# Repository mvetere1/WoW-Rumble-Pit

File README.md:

## Rumble Pit WoW Addon and hardware
### Objective: Make a device that can read data out of the world of warcraft game and adjust a motorized rumble pack based on damage done to give player live feedback 

#### Limitations
The game does not allow data to be streamed out while combat is happening.  Only after combat can logs etc be read to figure out damage done by the group.  Alledgely this is to deter botters from extracting too much data out of game live.  Addons are able to efficiently proceess data in-game to give good stats for group damage.

### 1. Initial Thoughts and Development
#### Motor Control
The motorized rumble pack control is pretty straightforward and not likely to change. A DC motor controller lets you control the speed of a motor by powering a high amperage motor with a low amperage signal from a micontroller.  The 293D is a really popular bidirectional motor control chip for <600ma at 4.5v-36v.   Using pulse-width modulation, you basically power the motor in short bursts.  The slower you want the motor, the longer the power is off.  If you want the max speed, the motor is powered 100% of the time.  So to control the motor speed, you just need a signal that you can vary the on/off state fairly quickly.  Sources for images can be found in Usefulinks.txt.

####  Potential Audio Output
Because you are limited to extracting data from the software in a non-live way, a method using hardware could be used instead.
* Data might be able to get exported from the game in the form of live running mp3.  A series of mp3 files could be made that encodes the desired level of vibration (based on damage) that is read by a microntroller directly controller the rumble pack.  I figure the mp3 file could be direct recordings of a UART sending out 0->10 in binary.
  * Pros: Should be a pretty reliable form of communication, it's easy to play mp3 files in-game through a certain audio port
  * Cons: Mp3s would need to get pre-recorded, one for each power level so it could add up to a lot of mp3
#### Potential Optical Output
* Data could be exported from the game optically. The game could print a box on the screen and flash the box black/white in a way that is encoding power level for the rumble pack motor.  The most efficient way would do this is without a microntroller, it could flash pulses of white/black with varying duty-cycles to control the motor at different speeds.  A type of light sensor would act as the optical-> voltage transducer and could be mounted to the monitor.  
  * Pros - No microcontroller needed, less steps for processing
  * Cons - Light sensor needs to be sensitive/tunable enough to detect on-screen changes.  Timing with LUA would need to be consistent
  
Alternatively, the flashing could try to emulate the entirety of UART and the bits could be read from a microcontroller with the UART peripheral.  
  * Pros - Sending 8 bit packets would open huge doors for sending arbitrary data out of the game, UART supported by 99% of micros
  * Cons - Light sensor needs to be sensitive/tunable for on-screen changes, timing would be critical to control.
  
A third way would be the have the box adjust the shade of black or white.  That shade of color would correlate to a rumble power level.  A color sensor could be mounted to the screen and send the data to a micro.
  * Pros - Should be able to get decent resolution with color shading.  Wouldn't require precise timing within LUA scripts
  * Cons - Color sensing might need a lite-calibration.  Output data format for color is probably more complicated than voltage.
  
### 2.Options tried
#### Optical LED transitor circuit
The first method I tried was the first listed optical choice.  I wanted to see if a simple light detector circuit would be sensitive enough to detect a white box vs a black box on a computer screen.  Since I had the parts, I went with the following:

Transitor used was a common NPN 2N222.  The most sensitive combination of parts I found was an orange LED and a 470k resistor.  The higher the R, the more gain.  When light of the same color hits the led, a small current is generated, so with the transistor applying a large gain, the voltage at the collector can vary up to Vp to respond to changes in light.  When the LED in this circuit has another LED of the same type blasting full strength right next to it, the voltage drops to 0v.  When in just ambient light, voltage is 5v.  So if the white box on the screen put out enough light, to drop voltage to 0, this the timing of the light pulses could be used to PWM the motor to the correct speed.

The issue is that the LCD monitor does not put out enough light at the right frequency to have any voltage response that could be used for PWM of the motor.  Potentially a light detector circuit that is more appropriate just an led and transistor would work better but that is unavailable right now.

#### Optical Color light to frequency converter
I tried a module based on the TSC3200 chip that is used as a color sensor.    

Based on the selection for pin S2 and S3, you can detect how much of that color is present where the sensor/chip is pointing. If I have it set to red, a full red color will produce 370hz while black would produce 250hz.  A decent oscilloscope will show you apprximate frequency of the output.  So if you have 10 divisions, each divisions would have a range of ~12hz.  You would probably need to sample for 100ms+ to get a good average of frequency but the 10 levels could probably be done.  

There's also the option of switching the full scale output frequency at 2%, 20% or 100%.  The faster the frequency, the quicker  you can get an average of 100 cycles for example but the sampling device would need to be able to keep up.  I chose 2% because that is still 250hz+ so 100 cycles could be sampled in 400ms, defintely fast enough for this application.  Updating the motor speed 2 times a second would be pretty smooth.

This method seems to be the most viable to far but it would probably need a type of calibration because once you change position of the sensor pointed on the screen, the min/max frequency changes.  Tt probably has to do with the positioning and reflection off the screen.  After installing on the screen with ambient lighting running, you would get the max and min frequency switching from red to black.  You would then need to program this back into the microcontroller thats calculating frequency so you can properly map max frequency to 100% duty cycle for max motor speed.  The min frequency would be 0% duty cycle, no motor speed.

I decided to go with the red color selection at 2% full scale frequency, and am planning for black to be ~250hz and red to be ~370hz.  Going with 10 divisions (10%, 20%, 30%.. etc motor strength) means each power level will have a 12hz bucket.  I am interpolating the data here but in reality it might not be so linear.  The equation is: % Duty cycle = (output frequenxy[hz] - 250[hz])(0.8[%]/[hz]).  This equation would change depending on the specific frequencies that red and black produce on that particular setup.

#### Microntroller Frequency Counting

The output of the sensor needs to be plugged into something that can convert the frequency into a PWN signal.  Based on the one off nature of this project, I'm going with an arduino uno.  
update 05Jun20

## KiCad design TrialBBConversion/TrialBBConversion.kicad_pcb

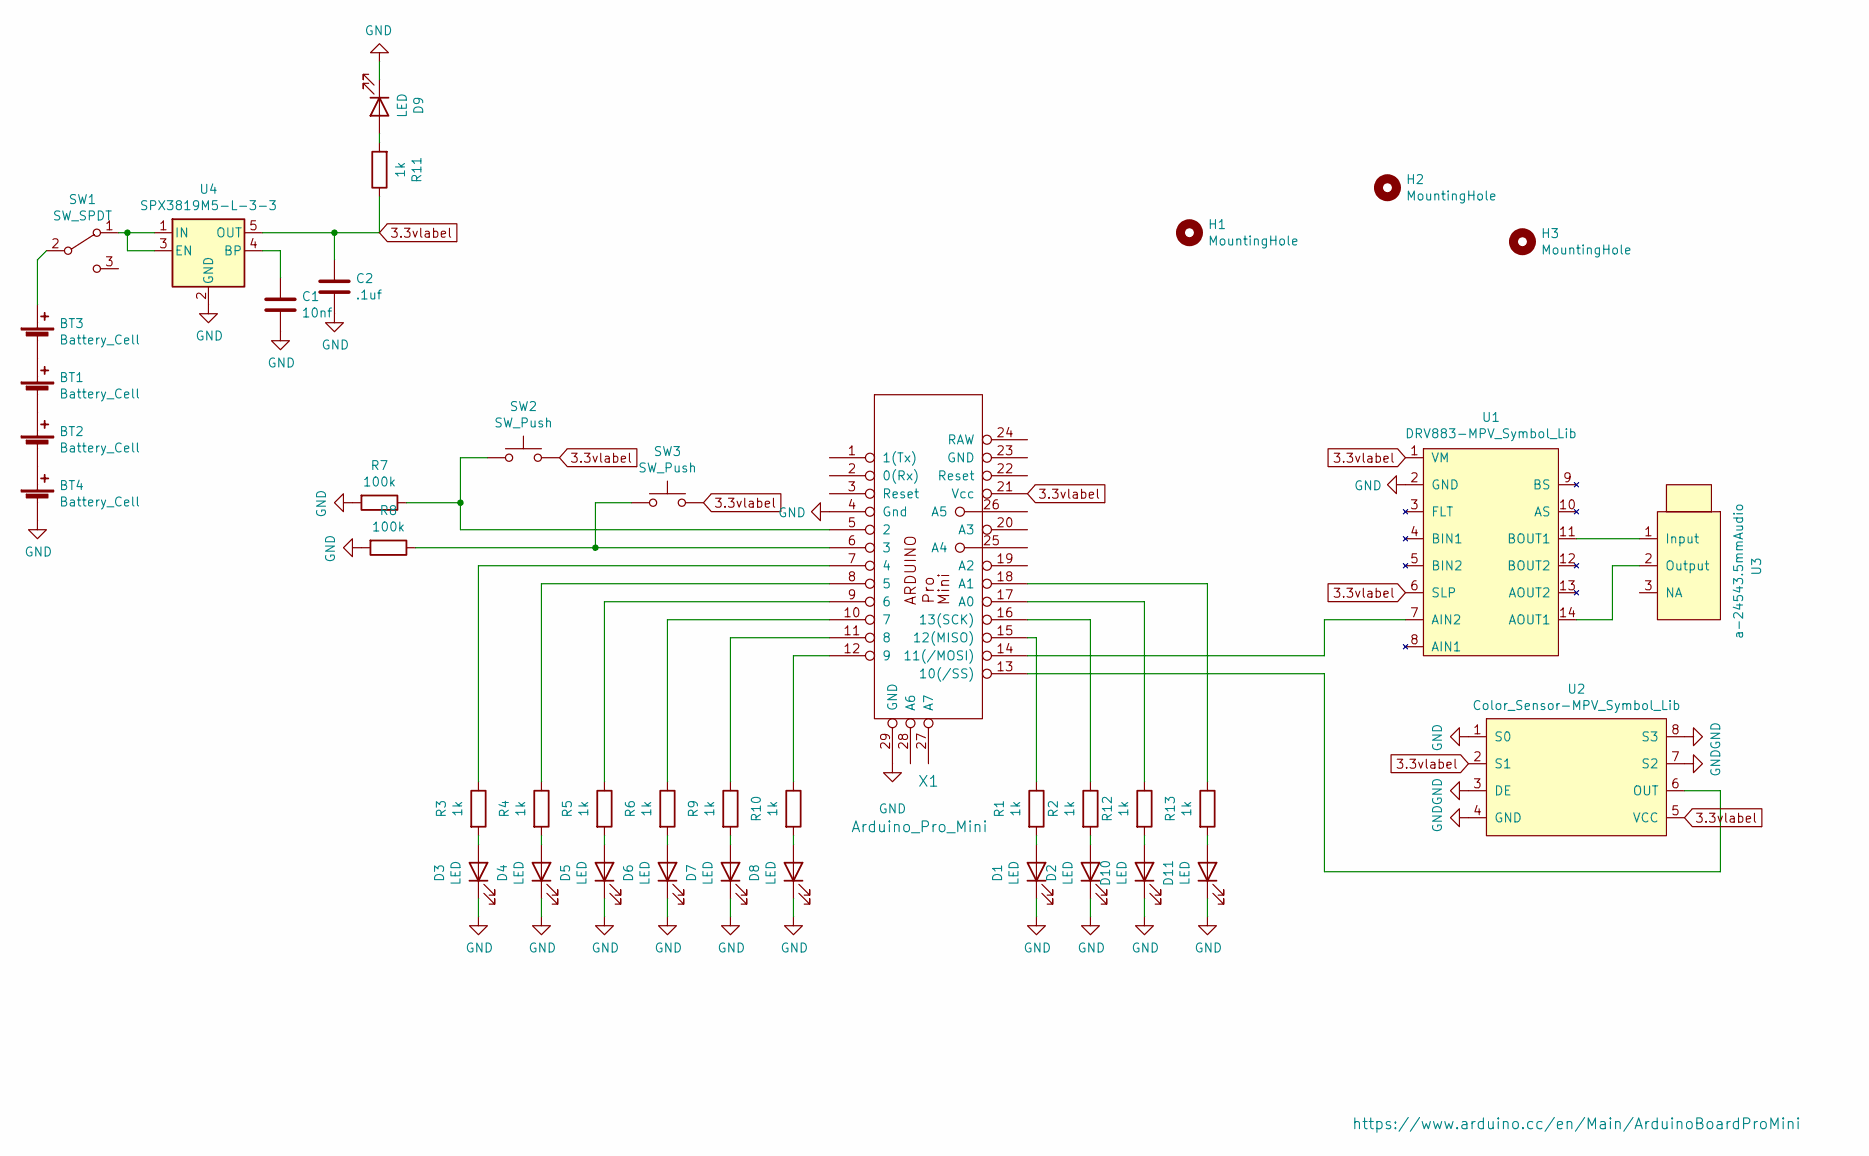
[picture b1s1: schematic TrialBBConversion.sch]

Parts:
BT1, BT2, BT3, BT4: Battery_Cell; BatteryHolder_Keystone_2466_1xAAA
C1: 10nf; C_1206_3216Metric_Pad1.42x1.75mm_HandSolder
C2: .1uf; C_1206_3216Metric_Pad1.42x1.75mm_HandSolder
D1, D2, D3, D4, D5, D6, D7, D8, D9, D10, D11: LED; 5730_LED_SMD
H1, H3: MountingHole; MountingHole_5.3mm_M5
H2: MountingHole; MountingHole_8.4mm_M8
R1, R2, R3, R4, R5, R6, R9, R10, R11, R12, R13: 1k; R_1206_3216Metric_Pad1.42x1.75mm_HandSolder
R7, R8: 100k; R_1206_3216Metric_Pad1.42x1.75mm_HandSolder
SW1: SW_SPDT; SPDT_Switch
SW2, SW3: SW_Push; Button_2_lead_SPST_TH
U1: DRV883-MPV_Symbol_Lib; DRV8833_Module
U2: Color_Sensor-MPV_Symbol_Lib; Color_Sensor
U3: a-24543.5mmAudio; 3.5mm_Audio_Jack_A-2454_Tayda
U4: SPX3819M5-L-3-3; SOT-23-5
X1: Arduino_Pro_Mini; pro_mini

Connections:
3.3vlabel: C2.1, R11.1, SW2.2, SW3.2, U1.1 (VM), U1.6 (SLP), U2.2 (S1), U2.5 (VCC), U4.5 (OUT), X1.21 (Vcc)
GND: BT4.2 (-), C1.2, C2.2, D1.1 (K), D2.1 (K), D3.1 (K), D4.1 (K), D5.1 (K), D6.1 (K), D7.1 (K), D8.1 (K), D9.1 (K), D10.1 (K), D11.1 (K), R7.2, R8.2, U1.2 (GND), U2.1 (S0), U2.3 (DE), U2.4 (GND), U2.7 (S2), U2.8 (S3), U4.2 (GND), X1.4 (Gnd), X1.29 (GND)
unnamed: BT1.1 (+), BT3.2 (-)
unnamed: BT1.2 (-), BT2.1 (+)
unnamed: BT2.2 (-), BT4.1 (+)
unnamed: BT3.1 (+), SW1.2 (B)
unnamed: C1.1, U4.4 (BP)
unnamed: D1.2 (A), R1.2
unnamed: D2.2 (A), R2.2
unnamed: D3.2 (A), R3.2
unnamed: D4.2 (A), R4.2
unnamed: D5.2 (A), R5.2
unnamed: D6.2 (A), R6.2
unnamed: D7.2 (A), R9.2
unnamed: D8.2 (A), R10.2
unnamed: D9.2 (A), R11.2
unnamed: D10.2 (A), R12.2
unnamed: D11.2 (A), R13.2
unnamed: R1.1, X1.15 (12(MISO))
unnamed: R2.1, X1.16 (13(SCK))
unnamed: R3.1, X1.7 (4)
unnamed: R4.1, X1.8 (5)
unnamed: R5.1, X1.9 (6)
unnamed: R6.1, X1.10 (7)
unnamed: R7.1, SW2.1, X1.5 (2)
unnamed: R8.1, SW3.1, X1.6 (3)
unnamed: R9.1, X1.11 (8)
unnamed: R10.1, X1.12 (9)
unnamed: R12.1, X1.17 (A0)
unnamed: R13.1, X1.18 (A1)
unnamed: SW1.1 (A), U4.1 (IN), U4.3 (EN)
unnamed: U1.7 (AIN2), X1.14 (11(/MOSI))
unnamed: U1.11 (BOUT1), U3.1 (Input)
unnamed: U1.14 (AOUT1), U3.2 (Output)
unnamed: U2.6 (OUT), X1.13 (10(/SS))

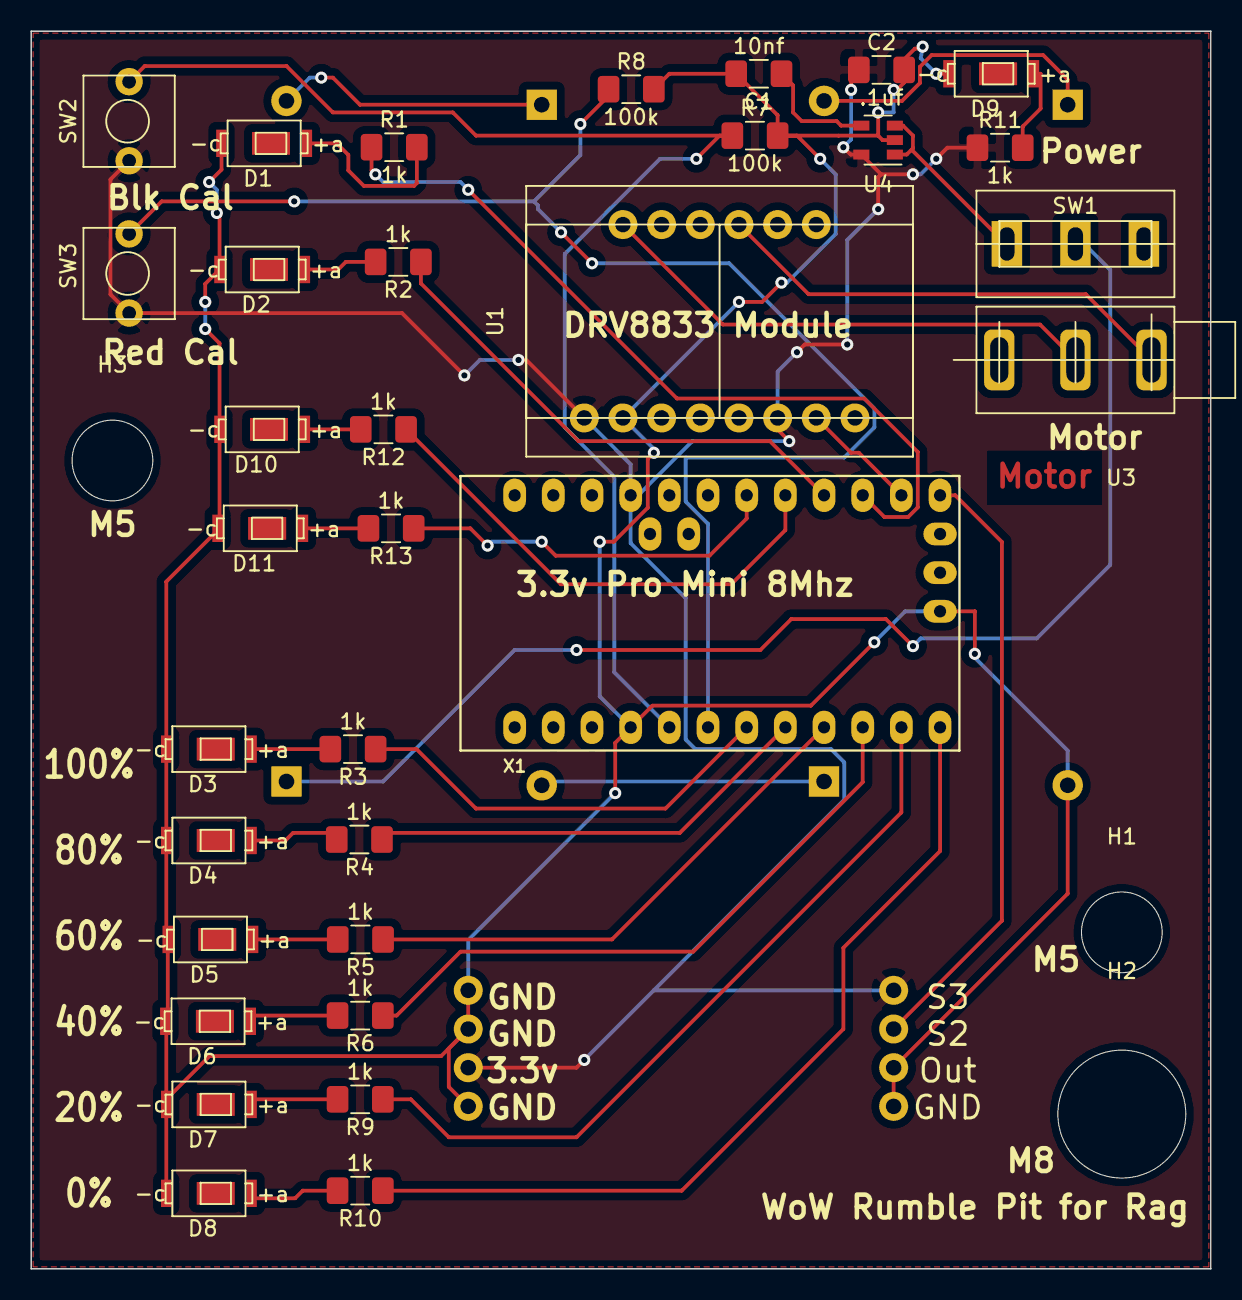
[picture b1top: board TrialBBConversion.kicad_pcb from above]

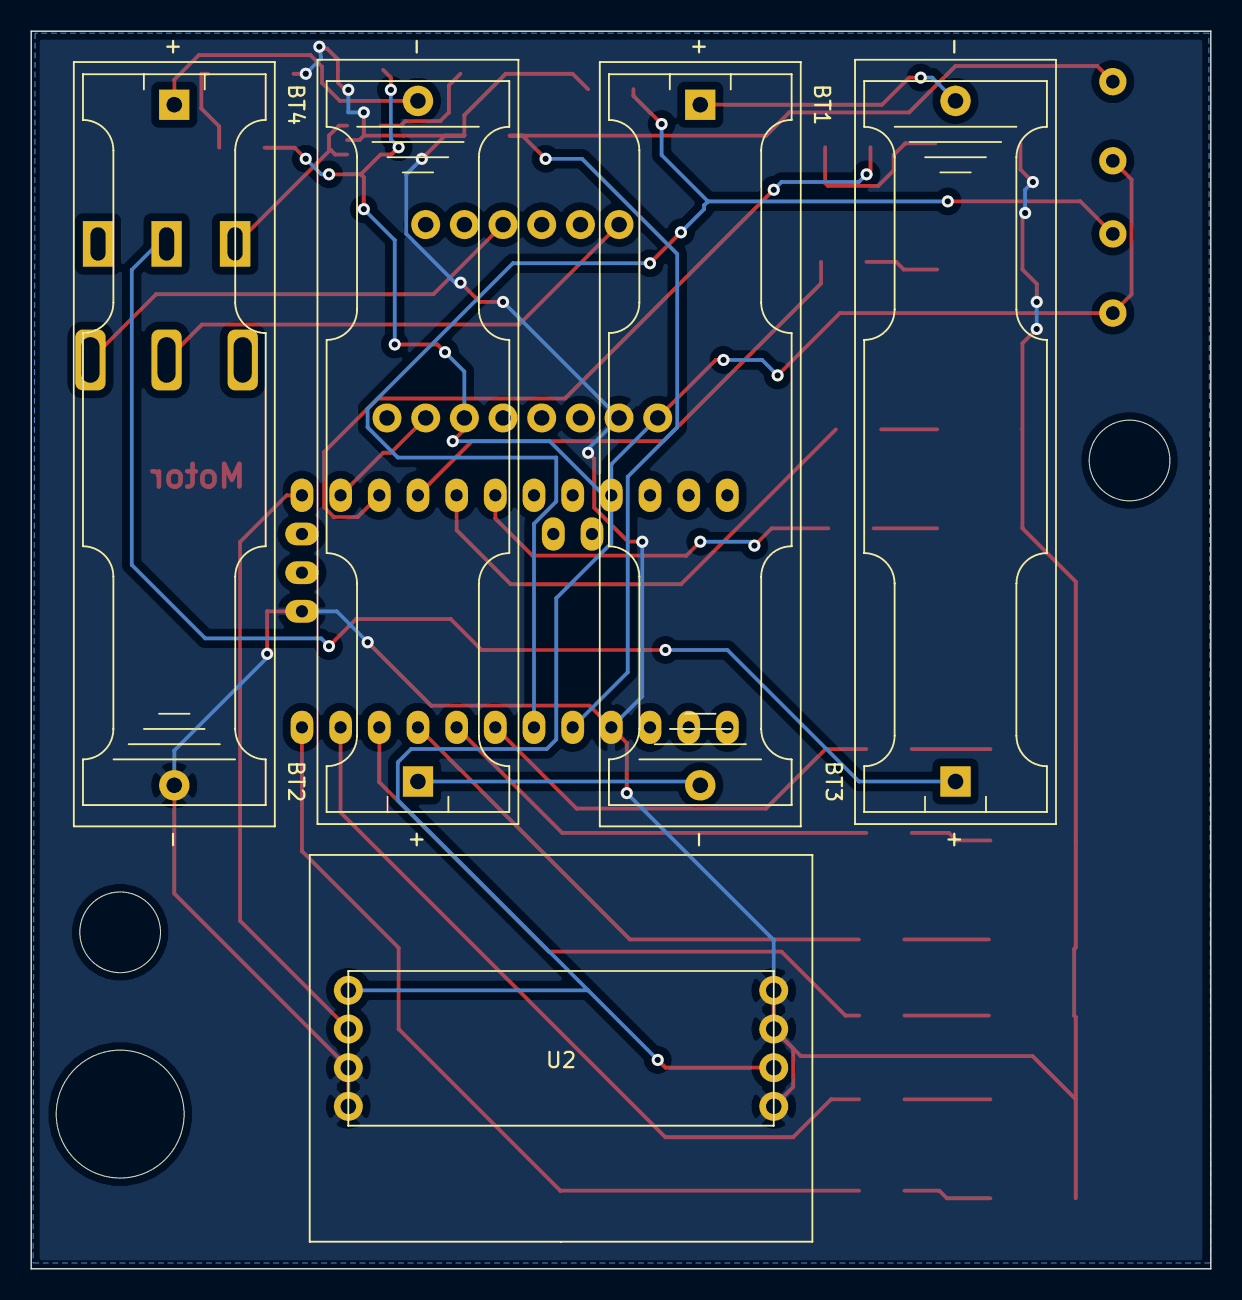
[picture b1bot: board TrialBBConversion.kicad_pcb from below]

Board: 2 copper layers, 77.5 x 81.3 mm, 41 parts (5 on the bottom side), 35 nets.

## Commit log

2020-01-01 New Files for LUA scripts
2020-01-01 New txt file for links referenced through build and random sound file for testing
2020-01-01 Adding Reference Pics
2020-01-01 changed pinout name
2020-01-02 changed pic name
2020-01-04 Added Calcs and frequency counter sketch
2020-01-04 Tested version
    tested with wow color wheel. Good response time on the scope. next step is to change the pwm frequency, right now it's around 490z
2020-01-04 register changes for slower PWM
2020-01-05 Update FrequencyCounter.ino
    working version while color sensor just pointed onto desk
2020-01-06 added new files and updates
2020-06-06 Create ModdedFreqCounterProMicro.ino
    Added dupilcate of sketch to get it running for the pro micro at 8Mhz
2020-06-06 this pro version appears to work
2020-06-07 refactoring
2020-06-08 mods
2020-06-13 overall improvements
2020-06-17 adding more kicad stuff
2020-06-17 updated routing pcb
2020-06-19 mostly improved silkscreen
2020-06-20 started BB project in github
2020-06-20 new stuff
2020-06-20 new gerbers
2020-07-02 did pcb layout and added some status stuff to code
2020-07-02 adjusted for current pcb layout
2020-07-22 additions to accomodate board layout
    remember the drv8833 needed two wires cus the symbol has the pins flipped on the motor output side. need to fix this in next rev
2022-07-27 Adding launcher
2022-08-01 New file and improved toc file
2023-02-05 Adding new proto file
2023-02-06 fixed object nil thing
2023-02-06 new test file
2023-02-06 fixes
2023-02-08 fixed box updating with rumble data
